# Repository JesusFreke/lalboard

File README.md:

##### lalboard - A 3D-printed keyboard inspired by the DataHand.

## Links
[More Images](https://github.com/JesusFreke/lalboard/wiki/Images)

[120 WPM Typing Demo](https://www.youtube.com/watch?v=oMhOIgrdeE0)

[V2 Project Logs (hackaday.io)](http://lalboard.com)

Online viewer for cluster assemblies:
- [finger](https://a360.co/3vxlLLL)
- [left thumb](https://a360.co/3c63TzE)
- [right thumb](https://a360.co/3c6tvws)

## Project Details
I am a long-time user of a DataHand keyboard. With the scarcity and rising cost of second hand
DataHands these days, I wanted to ensure that I always had access to a DataHand-like keyboard. And
so this project was born.

The overall functionality of the lalboard is obviously heavily based on the DataHand, but I designed
all of the specific key mechanisms, etc. from scratch, to be printable on a normal hobby-level
FDM printer.

With my DataHand, I never felt like I could get the keys positioned *quite right* for my hand. So
one of my primary focuses with the lalboard was adjustability. Each key cluster can be independently
adjusted in all 6 degrees of freedom to some extent.

Most parts need to be printed in a very opaque PLA, but there are a few parts that don't work well
in PLA which should be printed in polycarbonate or similar material, for its strength and heat
resistance.

##### Key Mechanisms

All keys use a pair of magnets to provide the clickiness and key return force, and an IR LED and
phototransistor for detecting a keypress. They are all held in place only with magnets, so they
are easily removable for cleaning, etc.

The feel/clickiness of the keys was another focus area. I tried to get them to feel as similar to
those on a DataHand as possible. They require roughly the same amount of force, and have that same
unique clicky feel due to the magnetic holding force.

##### Adjustability

The key clusters have a trio of standoffs that are designed to be mounted onto a steel sheet with
magnets. Each standoff has an adjustable height, and is mounted to the key cluster via a
ball socket. This provides a limited 6 degrees of freedom in adjusting the angle and position of
each key cluster, in order to get it perfectly positioned for your hands.

##### Electronics

This design uses copper traces that are cut from adhesive-backed copper tape using a vinyl cutter,
and applied to the bottom of 3D-printed "pcbs" printed with polycarbonate for its excellent heat
resistance during soldering. There are currently no designs for actual pcbs, but I don't think it
should be difficult to do. If someone wants to tackle that, I'm happy to give pointers or otherwise
help in any way I can :)

Each side of the keyboard uses an independent teensy 2.0 board, and are connected with 4 wires
between them to enable communication via i2c. Only one side of the keyboard actually needs to be
plugged into USB. The teensy's run a modified version of the
[teensyhand](https://github.com/JesusFreke/teensyhand) firmware.

##### Handrest

The handrest was first molded for my wrist in plasticine clay, and then scanned in using the
[meshroom](https://github.com/alicevision/meshroom) photogrammetry software. Since they were molded
for my wrists specifically, I'm not sure how "one-size-fits-all" they are, or how comfortable they
would be for someone else to use.

##### [BOM](https://github.com/JesusFreke/lalboard/wiki/BOM)

##### [Printing tips & instructions](https://github.com/JesusFreke/lalboard/wiki/Printing-tips-&-instructions)

##### [Preparing the Vinyl-cut PCBs](https://github.com/JesusFreke/lalboard/wiki/Vinyl-Cut-PCBs)

--------

Note: This is not an officially supported Google product.

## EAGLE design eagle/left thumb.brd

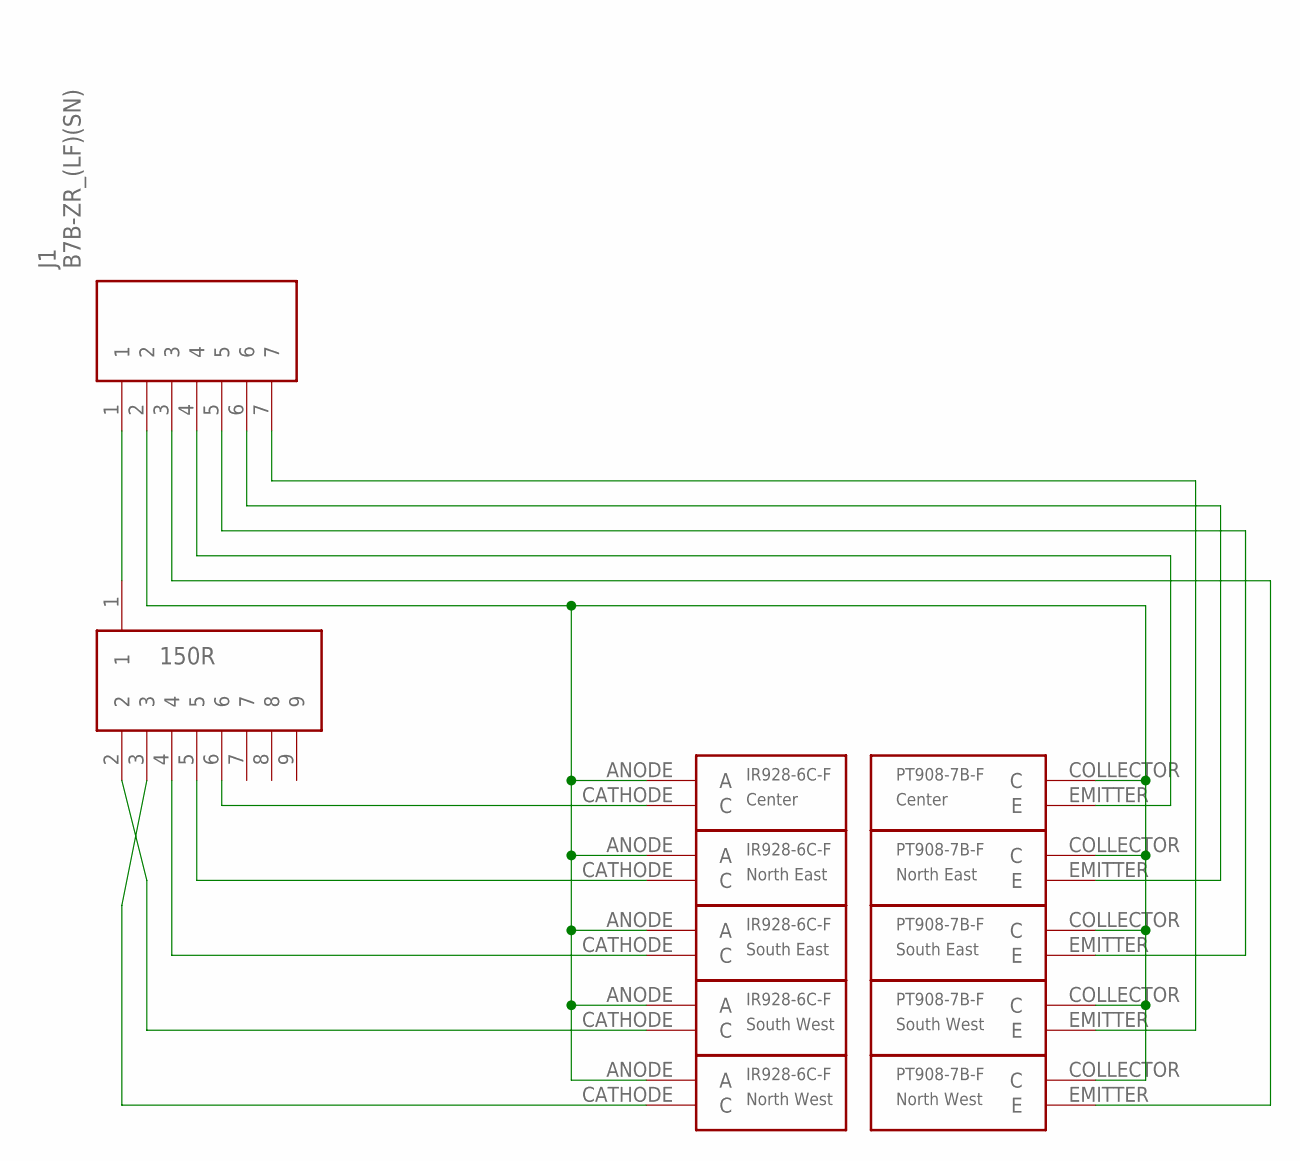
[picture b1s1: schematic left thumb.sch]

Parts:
J1: B7B-ZR_(LF)(SN); SHDR7W50P0X150_1X7_1200X350X45
LED1: Center; IR928-6C-F
LED2: North East; IR928-6C-F
LED3: South East; IR928-6C-F
LED4: South West; IR928-6C-F
LED5: North West; IR928-6C-F
PT1: Center; PT908-7B-F
PT2: North East; PT908-7B-F
PT3: South East; PT908-7B-F
PT4: South West; PT908-7B-F
PT5: North West; PT908-7B-F
RN1: 150R; 9PIN-RESISTOR-NETWORK

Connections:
unnamed: J1.1, RN1.1
unnamed: LED5.CATHODE (C), RN1.3
unnamed: LED4.CATHODE (C), RN1.2
unnamed: LED3.CATHODE (C), RN1.4
unnamed: LED2.CATHODE (C), RN1.5
unnamed: LED1.CATHODE (C), RN1.6
unnamed: J1.2, LED1.ANODE (A), LED2.ANODE (A), LED3.ANODE (A), LED4.ANODE (A), LED5.ANODE (A), PT1.COLLECTOR (C), PT2.COLLECTOR (C), PT3.COLLECTOR (C), PT4.COLLECTOR (C), PT5.COLLECTOR (C)
unnamed: J1.4, PT1.EMITTER (E)
unnamed: J1.6, PT2.EMITTER (E)
unnamed: J1.5, PT3.EMITTER (E)
unnamed: J1.7, PT4.EMITTER (E)
unnamed: J1.3, PT5.EMITTER (E)

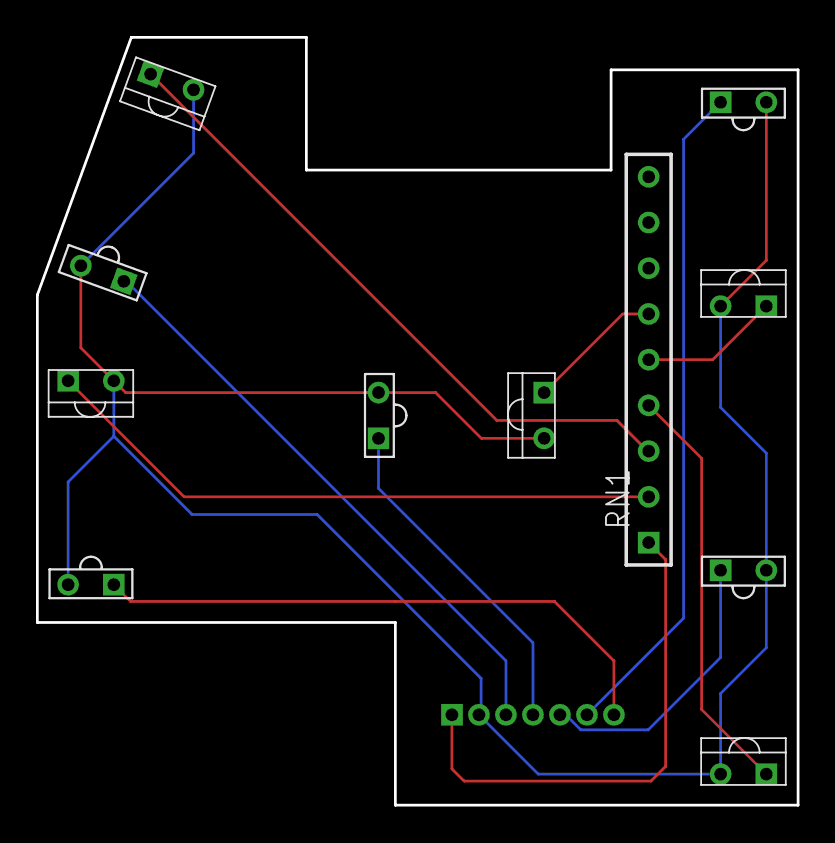
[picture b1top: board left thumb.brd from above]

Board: 2 copper layers, 42.3 x 42.7 mm, 12 parts (1 on the bottom side), 12 nets.

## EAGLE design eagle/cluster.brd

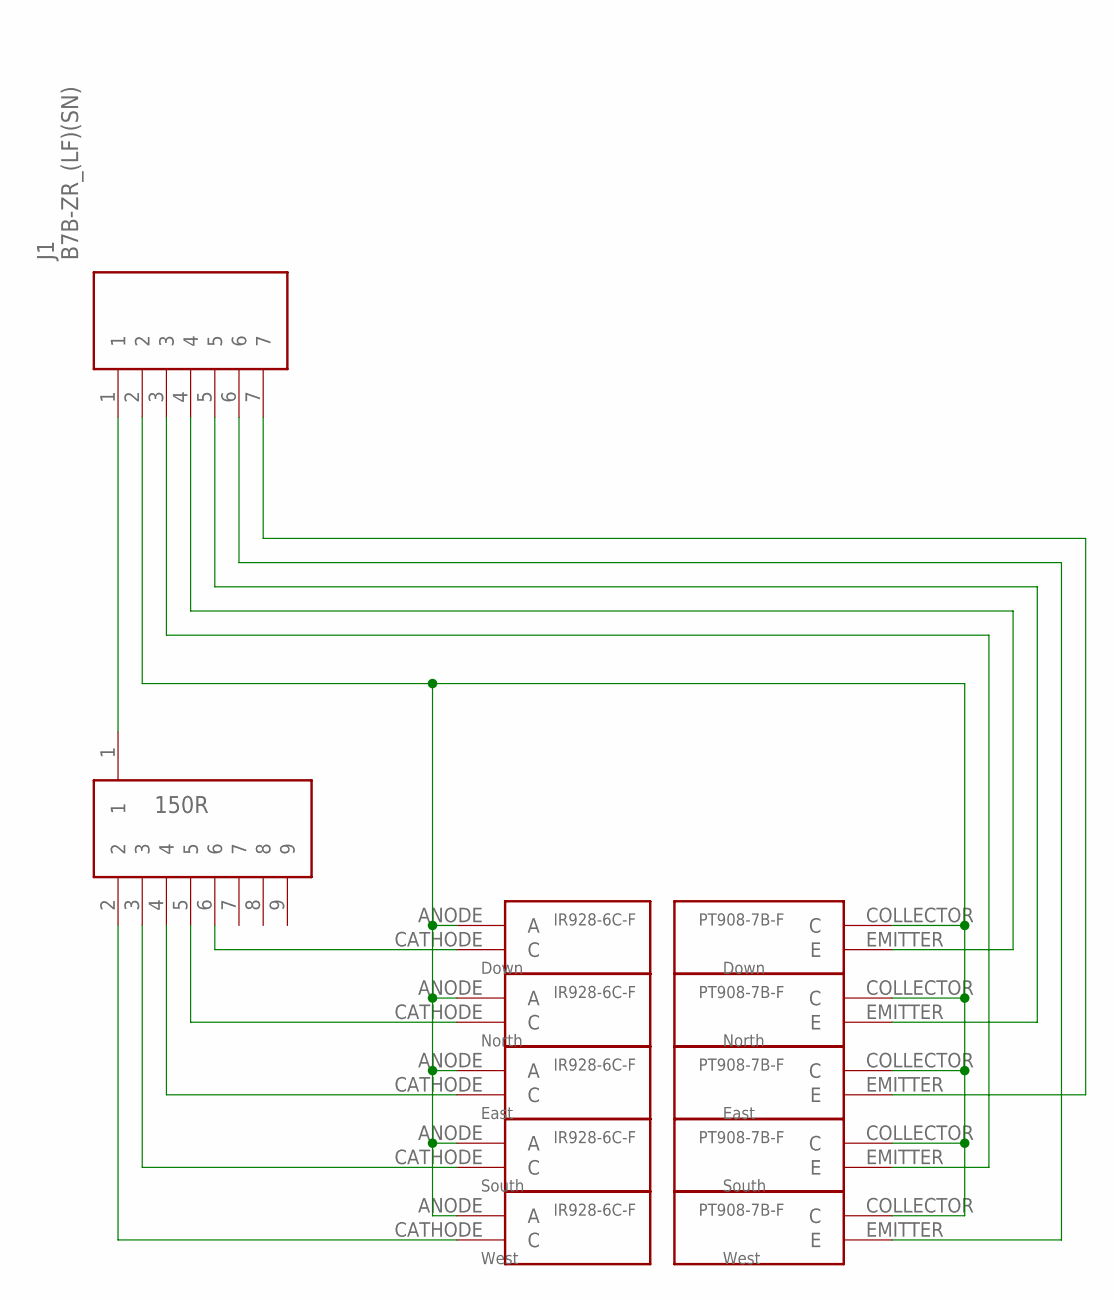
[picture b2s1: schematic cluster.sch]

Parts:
150R: 150R; 9PIN-RESISTOR-NETWORK
J1: B7B-ZR_(LF)(SN); SHDR7W50P0X150_1X7_1200X350X45
LED1: Down; IR928-6C-F
LED2: North; IR928-6C-F
LED3: East; IR928-6C-F
LED4: South; IR928-6C-F
LED5: West; IR928-6C-F
PT1: Down; PT908-7B-F
PT2: North; PT908-7B-F
PT3: East; PT908-7B-F
PT4: South; PT908-7B-F
PT5: West; PT908-7B-F

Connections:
unnamed: 150R.1, J1.1
unnamed: 150R.2, LED5.CATHODE (C)
unnamed: 150R.3, LED4.CATHODE (C)
unnamed: 150R.4, LED3.CATHODE (C)
unnamed: 150R.5, LED2.CATHODE (C)
unnamed: 150R.6, LED1.CATHODE (C)
unnamed: J1.2, LED1.ANODE (A), LED2.ANODE (A), LED3.ANODE (A), LED4.ANODE (A), LED5.ANODE (A), PT1.COLLECTOR (C), PT2.COLLECTOR (C), PT3.COLLECTOR (C), PT4.COLLECTOR (C), PT5.COLLECTOR (C)
unnamed: J1.3, PT4.EMITTER (E)
unnamed: J1.7, PT3.EMITTER (E)
unnamed: J1.5, PT2.EMITTER (E)
unnamed: J1.4, PT1.EMITTER (E)
unnamed: J1.6, PT5.EMITTER (E)

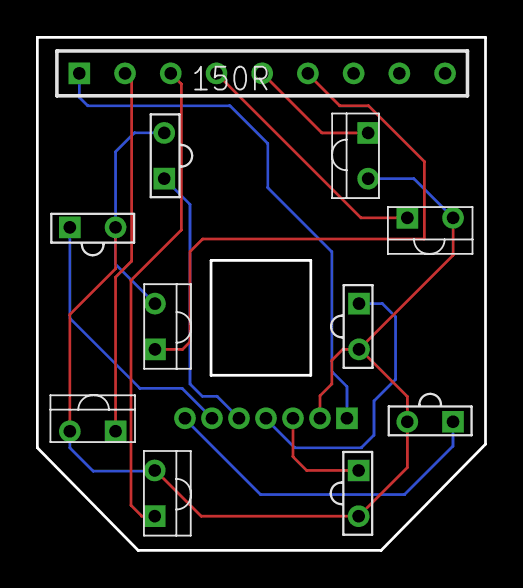
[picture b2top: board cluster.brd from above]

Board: 2 copper layers, 24.9 x 28.5 mm, 12 parts (1 on the bottom side), 12 nets.

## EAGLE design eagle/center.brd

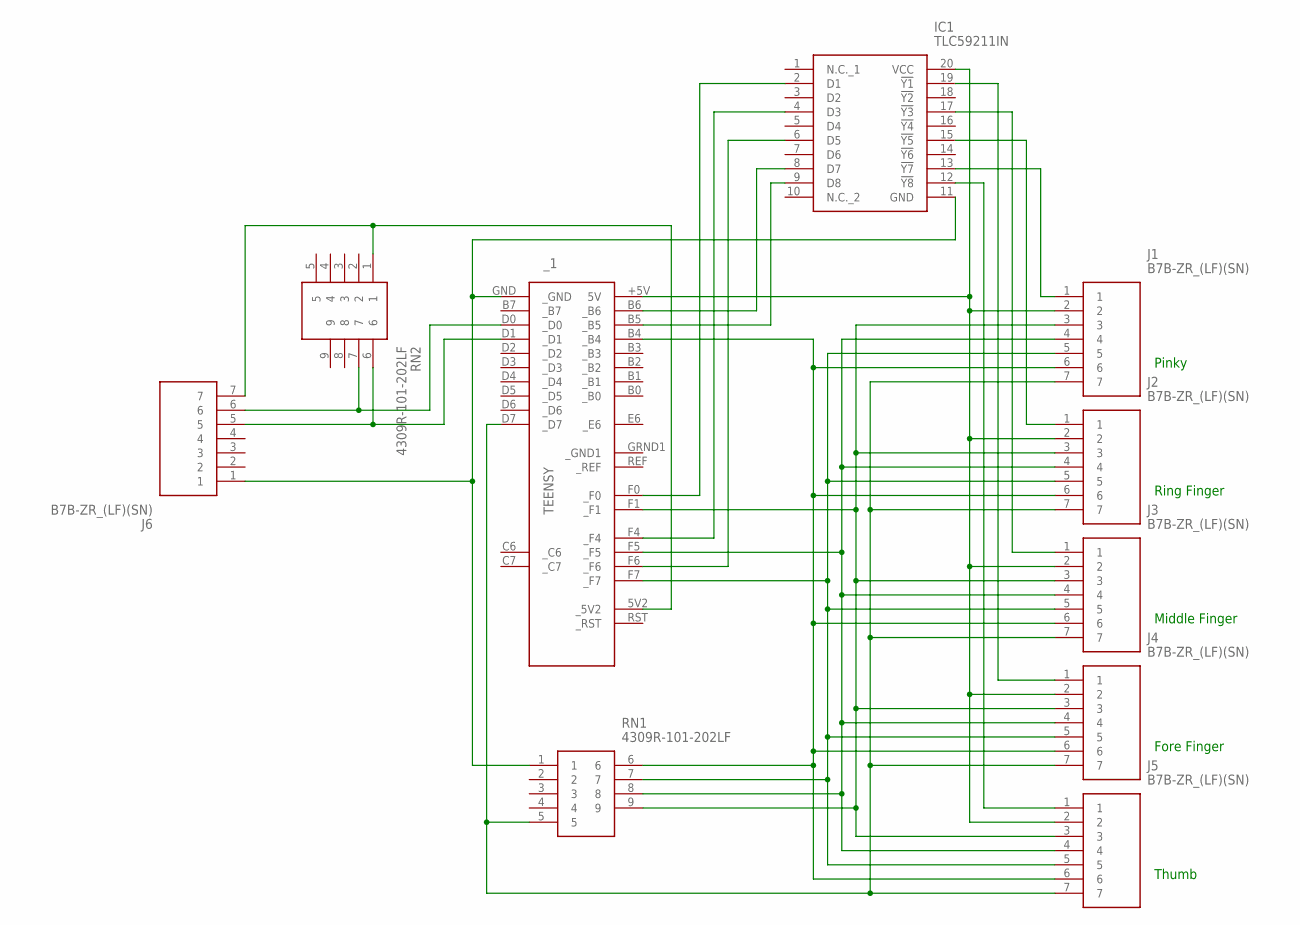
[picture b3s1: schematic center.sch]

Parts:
IC1: TLC59211IN; DIP794W53P254L2540H508Q20N
J1, J2, J3, J4, J5, J6: B7B-ZR_(LF)(SN); SHDR7W50P0X150_1X7_1200X350X45
RN1, RN2: 4309R-101-202LF; 4309R-101
_1: TEENSY

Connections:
unnamed: IC1.20 (VCC), J1.2, J2.2, J3.2, J4.2, J5.2, _1.+5V (5V)
unnamed: J1.3, J2.3, J3.3, J4.3, J5.3, RN1.9, _1.F1 (_F1)
unnamed: J1.6, J2.6, J3.6, J4.6, J5.6, RN1.6, _1.B4 (_B4)
unnamed: J1.4, J2.4, J3.4, J4.4, J5.4, RN1.8, _1.F5 (_F5)
unnamed: J1.5, J2.5, J3.5, J4.5, J5.5, RN1.7, _1.F7 (_F7)
unnamed: IC1.11 (GND), J6.1, RN1.1, _1.GND (_GND)
unnamed: J1.7, J2.7, J3.7, J4.7, J5.7, RN1.5, _1.D7 (_D7)
unnamed: IC1.8 (D7), _1.B6 (_B6)
unnamed: IC1.9 (D8), _1.B5 (_B5)
unnamed: IC1.6 (D5), _1.F6 (_F6)
unnamed: IC1.4 (D3), _1.F4 (_F4)
unnamed: IC1.2 (D1), _1.F0 (_F0)
unnamed: IC1.15 (!Y5), J2.1
unnamed: J6.5, RN2.6, _1.D1 (_D1)
unnamed: J6.7, RN2.1, _1.5V2 (_5V2)
unnamed: J6.6, RN2.7, _1.D0 (_D0)
unnamed: IC1.17 (!Y3), J3.1
unnamed: IC1.19 (!Y1), J4.1
unnamed: IC1.12 (!Y8), J5.1
unnamed: IC1.13 (!Y7), J1.1

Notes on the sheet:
Thumb
Pinky
Ring Finger
Middle Finger
Fore Finger

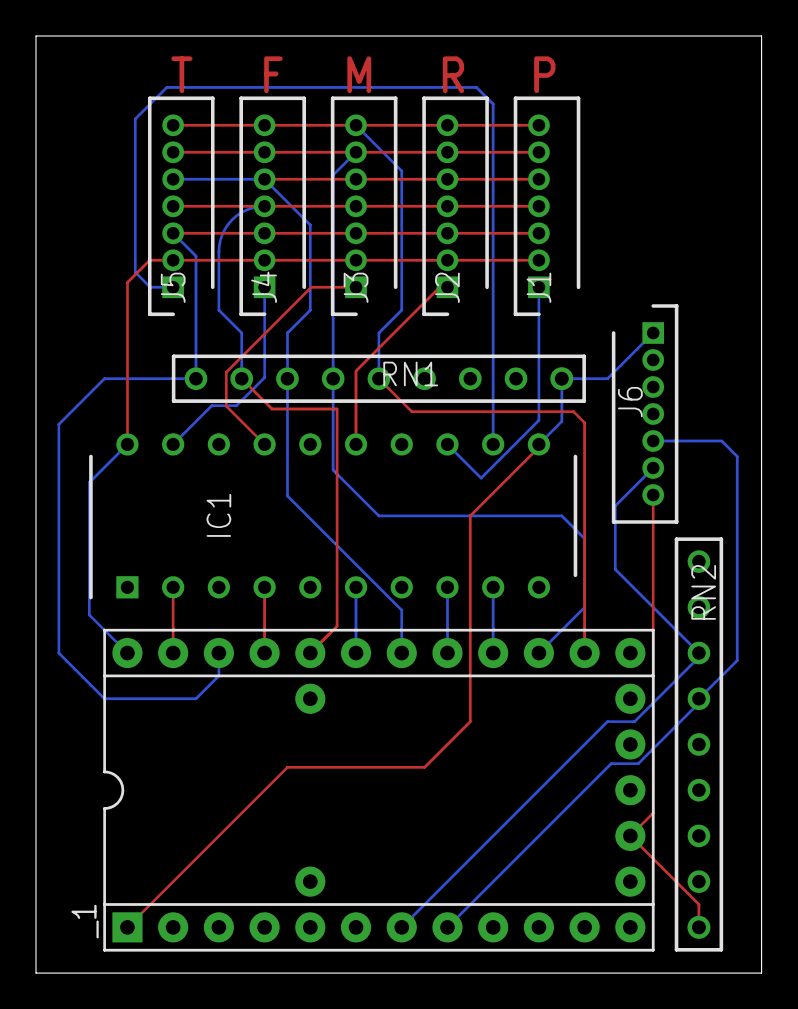
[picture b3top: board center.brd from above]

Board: 2 copper layers, 40.3 x 52.1 mm, 10 parts (0 on the bottom side), 20 nets.

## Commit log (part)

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2019-02-11 Initial side_key implementation
2019-02-11 Implement the center key
2019-02-11 Add initial key cluster, with 4 key bases
2019-02-11 Add the thumb pcb and the central pcb
2019-02-11 Tweak the retaining ridge geometry
2019-02-11 Tweak the thread size of the screwballs
2019-02-11 Tweak the hole size for the jst connector
2019-02-11 Tweak the retaining groove size and depth for the side keys
    This makes it a bit deeper, so the drooping overhangs don't fall all the
    way to the bed and prevent the groove from gripping.
    This also shrinks the width of the groove a bit, to give a bit more space
    between it and the magnet hole, for better printability
2019-02-11 Start implementing cluster with the initial 4 vertical key bases
2019-02-11 Fillet for the edges on the central magnet riser
    This should help reduce binding when pressing on the edge of the center
    key
2019-02-11 Redesign the thumb mode key
    This new design prevents the upward force by the thumb that was causing
    the previous design to slip out of the base.
2019-02-11 Reduce the key angle of the inner thumb key to 7
    I thought the previous angle of 10 felt good, but it turned out the key
    was stopping early, because it was hitting the key base of the mode key,
    so it wasn't actually moving the full 10 degrees.
2019-02-11 Add a key breakout board
    This has 2 JST connectors and a normal male header, which can be inserted
    between a key module and the central pcb, or between the two sides, to
    allow access to the signals for debugging purposes.
2019-02-11 Add the main thumb side keys
2019-02-11 Refactor how the led/phototransistor cavities are handled
    It now uses split faces that must be extended by the caller
2019-02-11 Add a thin base for the proximal ballsocket on the thumb module
2019-02-11 Tweak the design of the center key
    There's now a single post in the middle of the key, along with a protrusion
    to block the light when pressed. In the cluster, there's a central hole
    that the post is inserted in to.
    The post is also lengthened, so it extends to the bottom of the cluster in
    the neutral position, which requires a corresponding hole in the PCB now
    too.
2019-02-11 Don't return a separate negatives component from ball_socket_base
2019-02-11 Tweak the thin magnet cutout size, and use it for all screwball bases
2019-02-11 Add a longer ballscrew definition, for the back of the key modules
2019-02-12 Add exported stls for all of the models
2019-02-17 Create a docs folder and add some images
2019-02-23 Make the center down key post a square
    The previous circular post with a flat face had a tendency to get wedged
    into the hole if the key was rotated while pressing it
2019-02-25 Increase the height of the light interruptor on the center down key
    It wasn't blocking enough light to trigger the key
2019-02-28 Change the rotation of the magnet pair for the central down key back to horizontal
    The rotated magnet doesn't feel quite as clicky
2019-03-01 Get rid of the peaked magnet hole, and move the center magnets down a bit more
    The peaked magnet hole worked, but I didn't particularly like how it looked.
    This changes it back to the older squarish magnet hole.
    The nubbin on the center key was still interfering with the pliers a bit
    when inserting the magnet, so this also moves the magnets down a bit
    further.
2019-03-14 Increase the width of the groove on the back of the thumb mode key
    Due to the way the mode key in particular tends to get torqued, there would
    be an annoying click as the groove just catches on the corresponding ridge,
    and then slips past it.
2019-07-31 Add hand rest components
2019-08-01 Increase vertical space below board frame to account for longer Teensy pins
2019-08-08 Add board textures for rendering
2019-08-23 Reduce drill size of resistor holes. Fix right thumb cluster
2019-12-13 Add connection topic
    Also decrease image size
2019-12-15 Improve documentation
2020-06-29 Add a small cutout to help with inserting the "lower outer" magnet on the thumb
2020-06-29 Fix uses of Union.add
    This method was removed in fscad
2020-08-14 Fix the right handrest
    It was previously the same as the left hand side.
2020-10-10 Switch the clusters to use a new magnetic attachment mechanism
2020-10-18 Name the phototransistor and led cavities
2020-10-20 First part of making a solid top cluster
2020-10-20 Make the bottom of the key well a V instead of circular
    This makes the key well more easily printable upside-down without supports
2020-10-20 Make the light interruptor post on the center key a bit thinner
    The hole was made a bit thinner in the cluster refactor, and this helps
    to keep it from binding on the side
2020-10-26 Add a cutout for the connector legs on the underside of the cluster
2020-10-26 Add a cluster_assembly part script
    This creates the cluster, the pcb and the front and back clips in-situ.
2020-10-29 Starting design of new thumb cluster
2020-10-30 Add the remaining keys to the full thumb assembly
2020-11-01 Widen the slot behind the down key
    This allows easier insertion for the magnet in the lower outer key well.
    This also adds an extension to the back of the down key to cover over the
    extra gap, just so it looks nicer.
2020-11-01 Get rid of the old insertion cutout for the lower outer keywell
    The cutout wasn't present in the new design anyway, and I wasn't have
    any issues inserting the magnets without it.
2020-11-03 Move the kicad files up a directory
2020-11-03 Add kicad pcb design for left thumb
2021-03-09 Simplify the front of the cluster, and add a prototype cluster mount plate
2021-03-11 Restructure how the cluster parts are organized
    - rename the former "cluster_design" to "base_cluster_design"
    - add a new "cluster_design" that is only the base cluster, along with the front and back extensions
    - add the new front clip to cluster_assembly
2021-04-24 Extract stls directory into a submodule
2021-04-24 Extract the screw nut design out to a separate method in lalboard.py
    This allows it to be used in other assemblies without having to specify
    its parameters in multiple places.
2021-04-24 Fillet the center hole in the cluster pcb, and adjust its offset
2021-04-24 Update the exported thumb parts
2021-04-24 Fix the pad sizes on the cluster pcb design
    The custom sizes had apparently gotten lost in the last commit
    for the kicad stuff.
2021-04-24 Update the design of the left thumb cluster pcb
2021-04-24 Add nut recesses in the thumb clusters, for screws to hold down the PCB
2021-04-24 Fix up the cluster and thumb_cluster_left pcbs
    Some of the nets for the pours and screw holes had gotten unassigned
    somehow
2021-04-24 Fix the orientation of the magnet void in the base for the screw supports
    The void was flipped vertically, so that the widening insertion taper was
    at the bottom of the hole. This also embiggens the holes slightly, to make
    sure they're able to slip in.
2021-04-24 Add a bit more space at the lower outer part of the pcb
    This gives more space to get a trace out of that little cramped area
    in the bottom
2021-04-24 Fillet the remaining sharp corners on the thumb cluster
    It seems silly to have 2 sharp corners, with the rest being filleted
2021-04-24 Use cardinal directions as names for the cluster side key bases
    I think this is a bit clearer, and is the nomenclature I usually use when
    referring to a specific key.
2021-04-24 Add support for the filleted key wells to vertical_key_base
    Also refactor base_cluster_design to use this
2021-04-24 Fillet the keywells on the thumb clusters
2021-04-24 Add a fillet to the attachment cutouts on the thumb pcb
2021-04-28 Tweak the nut cutouts
    On the finger cluster, the nut cutout was 2.6mm tall, but it wasn't aligned
    with a .2mm layer line, so it was actually 2.8mm tall once sliced. This
    increases the size to 2.8mm and aligns it to a .2mm layer line.
    For the thumb clusters, the size was 2.6mm tall and it was already aligned,
    but 2.6mm was a bit too short and the nut didn't fit. This increases the
    size to 2.8mm.
2021-05-09 Tweak the thumb mode keys for better printability
    This adds a small "extension" to the beginning of the angled part that
    keeps it attached to the bed. The very first part of the slope up would
    always merge too strongly with the supports, leaving a bit of support
    material on the back.
    This gives a bit more vertical room at the point where the supports start,
    to help alleviate this problem.
2021-05-18 Update the handrest model to a brep based on a t-spline
    This is a t-spline that I modeled and fit to the original handrest mesh.
    The t-spline should be more easily editable if needed.
2021-05-22 Add a "bottom" named face for the central_pcb
    This avoids having to find the bottom face in the part script, and anywhere
    else it might be used.
2021-05-24 Add a full assembly for the left and right sides, using the new steel base
2021-05-29 Disable exporting assemblies to the cloud by default in export_parts
2021-06-01 Fix the thumb pcb for positioned_thumb_assembly for the left hand
2021-06-05 Remove some unused components and other dead code
2021-06-06 Reduce the travel angle of the thumb down key from 9 to 7 degrees
    The key was triggering a bit too early/releasing a bit too late, causing
    the shift key to accidentally be held down for a key after the intended
    key.
    This will cause the key to bottom out sooner, so that there should be less
    delay from starting to release the key to when it actually triggers the
    key up event.
2021-06-09 Reverse the cluster connectors on the main board
    This reverses the connectors, so the orientation is correct for a normally
    wired cable.
2021-06-14 Add a light interruptor on the bottom of the thumb down key
    This adds a small protrusion on the bottom that ensures the light path is
    fully blocked when the key is fully pressed.
2021-06-14 Update the stls for the recent changes to the thumb cluster
2023-10-10 Add a front magnet to the clusters
    Add a magnet, instead of that silly clip thing.
    An extra clip on the front isn't normally needed now, but one can
    be added in cases where the front of the cluster is too low to the
    base plate, to give a bit more room for the support underneath.
    This also tweaks the static supports to have another magnet at the
    front to attach to the cluster, and moves the cord slot a bit, to
2023-10-30 Update the main board for v2.5
    This switches from an ESP32 MCU to an RP2040
2023-11-18 Main board v2.5.1
    - Remove the decoupling capacitor on the boot selection button
    - Fix the part selection in the BOM for the 27 ohm usb series resistors
    (old part was mistakenly a 27kohm resistor)
